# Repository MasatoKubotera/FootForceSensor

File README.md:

<html lang="en">
  <head>
    <meta charset="uft-8">
    <meta name="author" content="Masato Kubotera">
  </head>
  <body>
    <h1>FootForceSensor Ver. 1.0</h1>
    <h2>About FootForceSensor</h2>
    <p>
      FootForceSensor is a sensor that measures the pressure applied to the sole of a biped robot's foot by attaching strain gauges (load cells) to four locations on each foot.<br>
      It is under development to detect the position of the robot's center of gravity and to improve gait control.
      <h3>About Ver. 1.0</h3>
      The values of the four strain gages can be read by the Pro Micro (usable as an Aruduino Leonardo) and transferred to the computer board via a USB interface or a 3.3V system RS-485 interface to which Kondo's B3M servo motors can be connected.<br>
      Power can be supplied from the same connector as one communication, from USB bus power in the case of USB interface communication, or from Kondo's B3M servo motor connector in the case of RS-485 interface communication.<br>
      To allow left and right legs to use the same firmware, a shortland is grounded on the board to identify left and right.
      <table>
        <tr>
          <td>
            <a href="image/brd_top.png">
              <div align="center">
                
              </div>
            </a>
          </td>
          <td>
            <div align="center">
              under construction<br>
              
            </div>
          </td>
        </tr>
        <tr>
          <td>
            <div align="center">
              PCB preview image
            </div>
          </td>
          <td>
            <div align="center">
              After component mounting
            </div>
          </td>    
        </tr>
      </table>
    </p>
    <h2>Repository Contents</h2>
    <p>
    <dl>
      <dt>\image</dt>
      <dd>PCB preview images and capture of design screen</dd>
      <dt>\libraries</dt>
      <dd>Libraries used in Autodesk Eagle design</dd>
      <dt>Schematic.pdf</dt>
      <dd>Circuit diagram of this product</dd>
      <dt>BOM.txt</dt>
      <dd>Parts lists output from design data</dd>
      <dt>.brd</dt>
      <dd>Board wiring design file by Autodesk Eagle</dd>
      <dt>.sch</dt>
      <dd>Schematic design file by Autodesk Eagle</dd>
      <dt>Gerber_data.zip</dt>
      <dd>Zip folder of Gerber format files for PCB manufacturing requests.</dd>
      <dt>LICENSE</dt>
      <dd>This is a license to use this product. Please confirm before use.</dd>
      <dt>.gitignore</dt>
      <dd>File to exclude cache files from management.</dd>
    </dl>
    </p>
    <h2>Documentation</h2>
      <p>
        <h3>BOM</h3>
          <table>
            <thead>
              <tr>
                <th> Eagle Design Parts # </th>
                <th> Q'ty </th>
                <th> Mfr. Product # </th>
                <th> Supplier </th>
                <th> Description </th>
              </tr>
            </thead>
            <tbody>
              <tr>
                <td> C1, C2, C3, C5, C6, C8, C9, C10, C12, C13, C14, C16 </td>
                <td> 12 </td>
                <td> GRM188R71E105KA12 </td>
                <td> <a href="https://akizukidenshi.com/catalog/g/gP-14526/">Akizuki</a> </td>
                <td> Multilayer Ceramic Capacitors SMD/SMT 1uF 25V 10% 0603 </td>
              </tr>
              <tr>
                <td> C18, C19, C20, C21 </td>
                <td> 4 </td>
                <td> GRM188R6YA106MA73 </td>
                <td> <a href="https://akizukidenshi.com/catalog/g/gP-13161/">Akizuki</a> </td>
                <td> Multilayer Ceramic Capacitors SMD/SMT 10uF 35V 20% 0603 </td>
              </tr>
              <tr>
                <td> C4, C7, C11, C15, C17 </td>
                <td> 5 </td>
                <td> GCM188L81H104K57 </td>
                <td> <a href="https://akizukidenshi.com/catalog/g/gP-16143/">Akizuki</a> </td>
                <td> Multilayer Ceramic Capacitors SMD/SMT 0.1uF 50V 10% 0603 </td>
              </tr>
              <tr>
                <td> CH1, CH2, CH3, CH4, CH5 </td>
                <td> 5 </td>
                <td> S4B-XH-A(LF)(SN) </td>
                <td> <a href="https://akizukidenshi.com/catalog/g/gC-12842/">Akizuki</a> </td>
                <td> Connector Header Through Hole, Right Angle 4 position 2.5mm </td>
              </tr>
              <tr>
                <td> IC1, IC2, IC3, IC4 </td>
                <td> 4 </td>
                <td> HX711 </td>
                <td> <a href="https://akizukidenshi.com/catalog/g/gI-12473/">Akizuki</a> </td>
                <td> 24-Bit Analog-to-Digital Converter (ADC) for Weigh Scales </td>
              </tr>
              <tr>
                <td> IC5 </td>
                <td> 1 </td>
                <td> ADM3078E </td>
                <td> <a href="https://www.mouser.jp/ProductDetail/584-ADM3078EARZ">Mouser</a> </td>
                <td> RS-485/RS-422 Transceiver (Half Duplex, 16 Mbps, DE/RE) </td>
              </tr>
              <tr>
                <td> LED1, LED2, LED3 </td>
                <td> 3 </td>
                <td> 150060VS86000 </td>
                <td> <a href="https://www.mouser.jp/ProductDetail/710-150060VS86000">Mouser</a> </td>
                <td> Standard LEDs - SMD Green 2V 20mA 573nm 0603 </td>
              </tr>
              <tr>
                <td> M1 </td>
                <td> 1 </td>
                <td> DEV-12640 </td>
                <td> <a href="https://www.mouser.jp/ProductDetail/474-DEV-12640">Mouser</a> </td>
                <td> Development Boards & Kits - AVR Pro Micro - 5V/16MHz </td>
              </tr>
              <tr>
                <td> M1 </td>
                <td> 1 </td>
                <td> 6604S-40 </td>
                <td> <a href="https://akizukidenshi.com/catalog/g/gP-01591/">Akizuki</a> </td>
                <td> 2.54mm Pin Socket Strip, Single Row </td>
              </tr>
              <tr>
                <td> M1 </td>
                <td> 1 </td>
                <td> PHA-1x40SG </td>
                <td> <a href="https://akizukidenshi.com/catalog/g/gC-06631/">Akizuki</a> </td>
                <td> 2.54mm Pin Header Strip, Straight, Single Row </td>
              </tr>
              <tr>
                <td> R1, R4, R7, R10 </td>
                <td> 4 </td>
                <td> RC0603FR-1320KL </td>
                <td> <a href="https://www.mouser.jp/ProductDetail/603-RC0603FR-1320KL">Mouser</a> </td>
                <td> Thick Film Resistors - SMD 20 kOhms 100-200mW 1% 0603 </td>
              </tr>
              <tr>
                <td> R13, R14, R15, R16, R17, R18 </td>
                <td> 6 </td>
                <td> RC0603FR-1010KL </td>
                <td> <a href="https://www.mouser.jp/ProductDetail/603-RC0603FR-1010KL">Mouser</a> </td>
                <td> Thick Film Resistors - SMD 10 kOhms 100-200mW 1% 0603 </td>
              </tr>
              <tr>
                <td> R19, R21 </td>
                <td> 2 </td>
                <td> RC0603FR-10680RL </td>
                <td> <a href="https://www.mouser.jp/ProductDetail/603-RC0603FR-10680RL">Mouser</a> </td>
                <td> Thick Film Resistors - SMD 680 Ohms 100-200mW 1% 0603 </td>
              </tr>
              <tr>
                <td> R2, R5, R8, R11 </td>
                <td> 4 </td>
                <td> RC0603FR-138K2L </td>
                <td> <a href="https://www.mouser.jp/ProductDetail/603-RC0603FR-138K2L">Mouser</a> </td>
                <td> Thick Film Resistors - SMD 8.2 kOhms 100-200mW 1% 0603 </td>
              </tr>
              <tr>
                <td> R20 </td>
                <td> 1 </td>
                <td> RC0603FR-10120RL </td>
                <td> <a href="https://www.mouser.jp/ProductDetail/603-RC0603FR-10120RL">Mouser</a> </td>
                <td> Thick Film Resistors - SMD 120 Ohms 100-200mW 1% 0603 </td>
              </tr>
              <tr>
                <td> R3, R6, R9, R12, R22, R23, R24 </td>
                <td> 7 </td>
                <td> RC0603FR-101KL </td>
                <td> <a href="https://www.mouser.jp/ProductDetail/603-RC0603FR-101KL">Mouser</a> </td>
                <td> Thick Film Resistors - SMD 1 kOhms 100-200mW 1% 0603 </td>
              </tr>
              <tr>
                <td> T1, T2, T3, T4 </td>
                <td> 4 </td>
                <td> MMBT3906 </td>
                <td> <a href="https://akizukidenshi.com/catalog/g/gI-05967/">Akizuki</a> </td>
                <td> Bipolar Transistors - BJT Bipolar Transistor, SOT-23, 40V, 200mA, PNP </td>
              </tr>
              <tr>
                <td> T5, T6, T7 </td>
                <td> 3 </td>
                <td> BSS138 </td>
                <td> <a href="https://akizukidenshi.com/catalog/g/gI-04232/">Akizuki</a> </td>
                <td> 50V N-Channel Enhancement Mode MOSFET - ESD Protected </td>
              </tr>
              <tr>
                <td> U1 </td>
                <td> 1 </td>
                <td> LM1117GS-3.3 </td>
                <td> <a href="https://akizukidenshi.com/catalog/g/gI-16989/">Akizuki</a> </td>
                <td> LDO Voltage Regulator 3.3V 1A </td>
              </tr>
              <tr>
                <td> U2 </td>
                <td> 1 </td>
                <td> LD1117S50 </td>
                <td> <a href="https://akizukidenshi.com/catalog/g/gI-15255/">Akizuki</a> </td>
                <td> LDO Voltage Regulator 5.0V 0.8A </td>
              </tr>
            </tbody>
          </table>          
        <h3>PCB Fabrication</h3>
          PCB(Printed Circuit Board) manufacturing was outsourced to <a href="https://www.elecrow.com/pcb-manufacturing.html">Elecrow</a>.<br>
          The custom specifications are as follows.
          <ul>
            <li>Layer : 2 layers</li>
            <li>Dimensions : 50 x 40</li>
            <li>Different PCB Design : 1eg</li>
            <li>PCB Thickness : 1.6</li>
            <li>PCB Color : Black</li>
            <li>Surface Finish : HASL</li>
            <li>Castellated Hole : No</li>
            <li>Copper Weight : 1oz</li>
            <li>PCB Stencil : Stencil 10cm X 10cm no frame[Top]</li>
          </ul>
          The data used to order fabrication are as follows.
          <ul>
            <li>Eagle design rule : <a href="https://www.elecrow.com/download/Elecrow_PCB_eagle_rule.zip">Elecrow Eagle Design Rule</a></li>
            <li>Eagle CAM file : <a href="https://www.elecrow.com/download/Elecrow_Gerber_Generater_DrillAlign.zip">Elecrow CAM file</a></li>
            <li>Gerber format data : <a href="/Gerber_data.zip">Gerber_data.zip</a></li>
          </ul>
      </p>
    <h2>Contact</h2>
    <p>
    If you have any questions, please contact MasatoKubotera, the product's designer, by E-mail.<br>
    E-mail : <a href="mailto:masatokubotera06@yahoo.co.jp">masatokubotera06@yahoo.co.jp</a>
    </p>
    <h2>License Information</h2>
    <p>
      This product is open source.<br>
      Please review the <a href="/LICENSE">LICENSE file</a> for license information.<br>
      <br>
      <strong>FootForceSensor Ver. 1.0</strong> by Masato Kubotera is licensed under a <a href="http://creativecommons.org/licenses/by-nc-sa/4.0/">Creative Commons Attribution-NonCommercial-ShareAlike 4.0 International License</a>.
    </p>    
  </body>
</html>

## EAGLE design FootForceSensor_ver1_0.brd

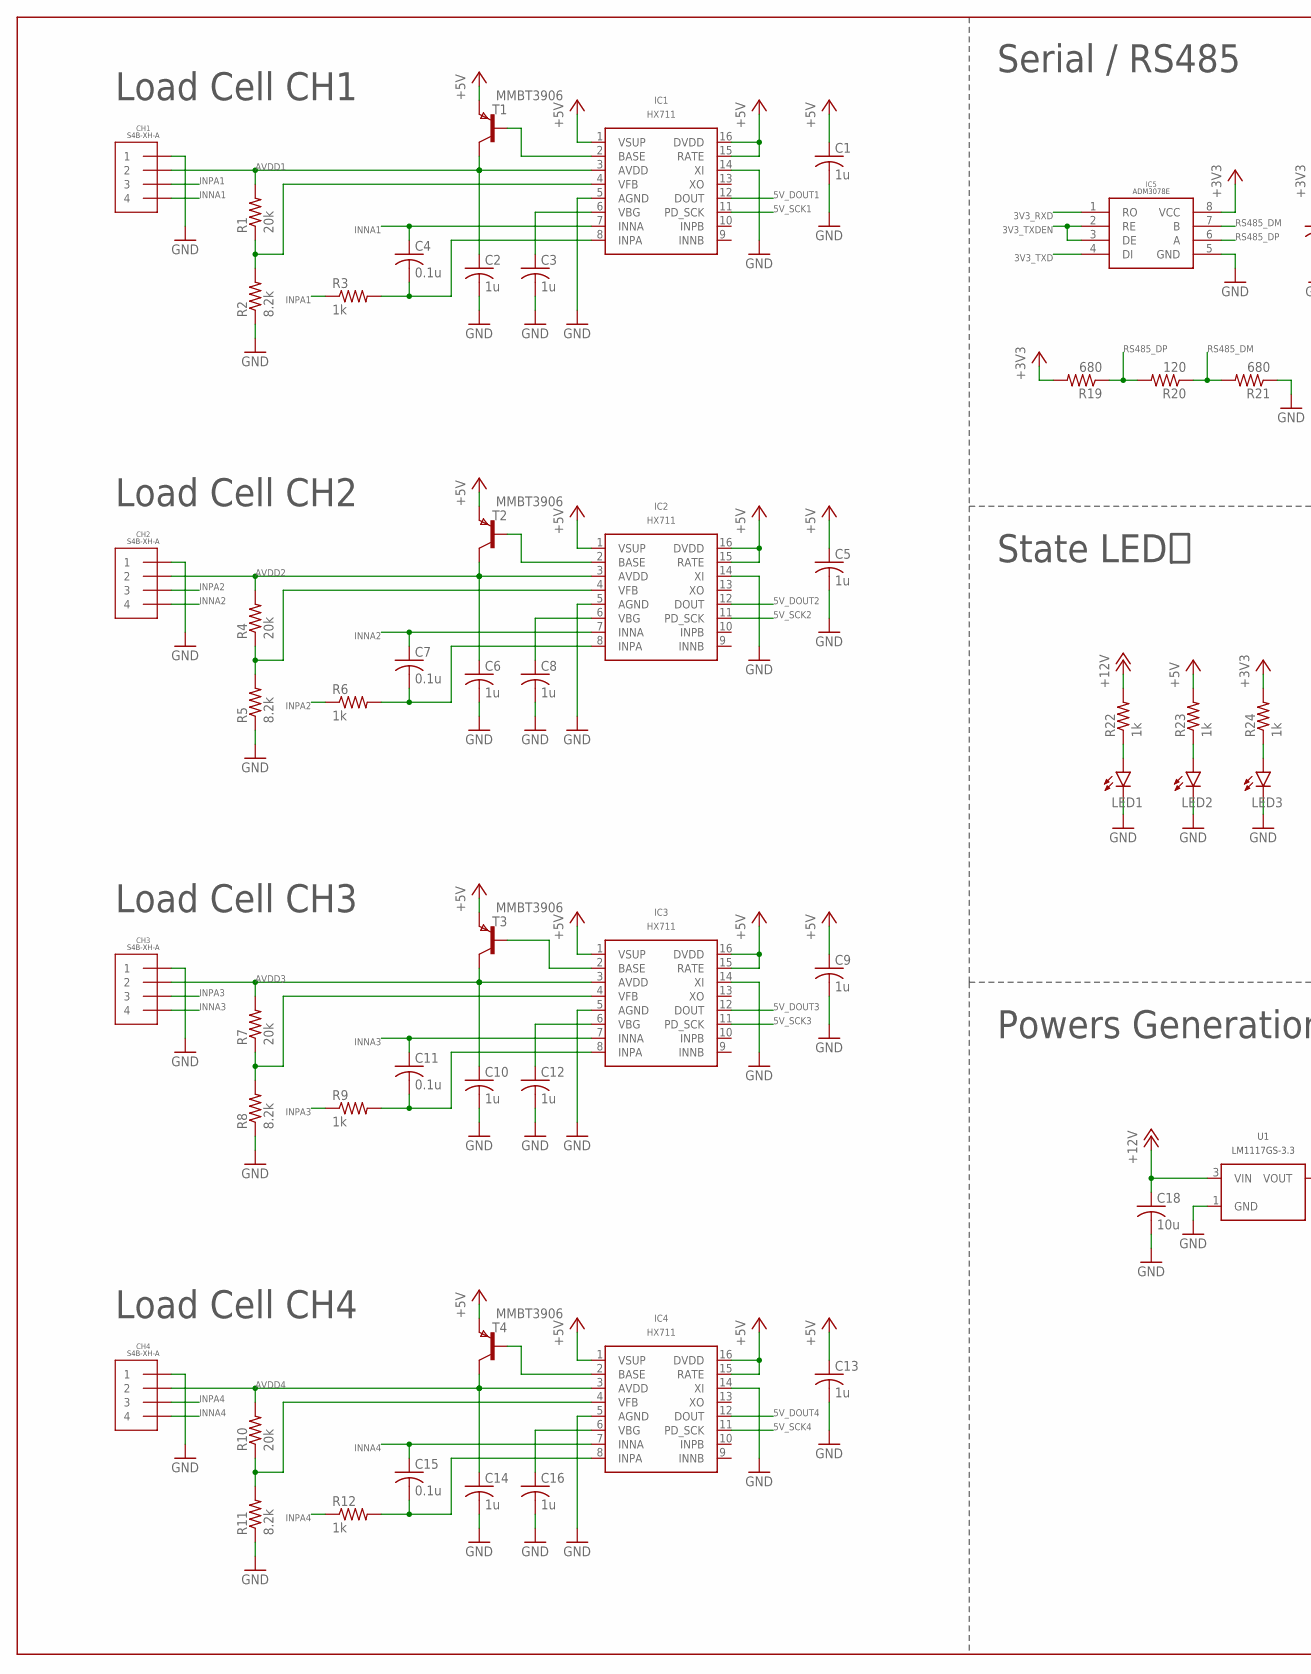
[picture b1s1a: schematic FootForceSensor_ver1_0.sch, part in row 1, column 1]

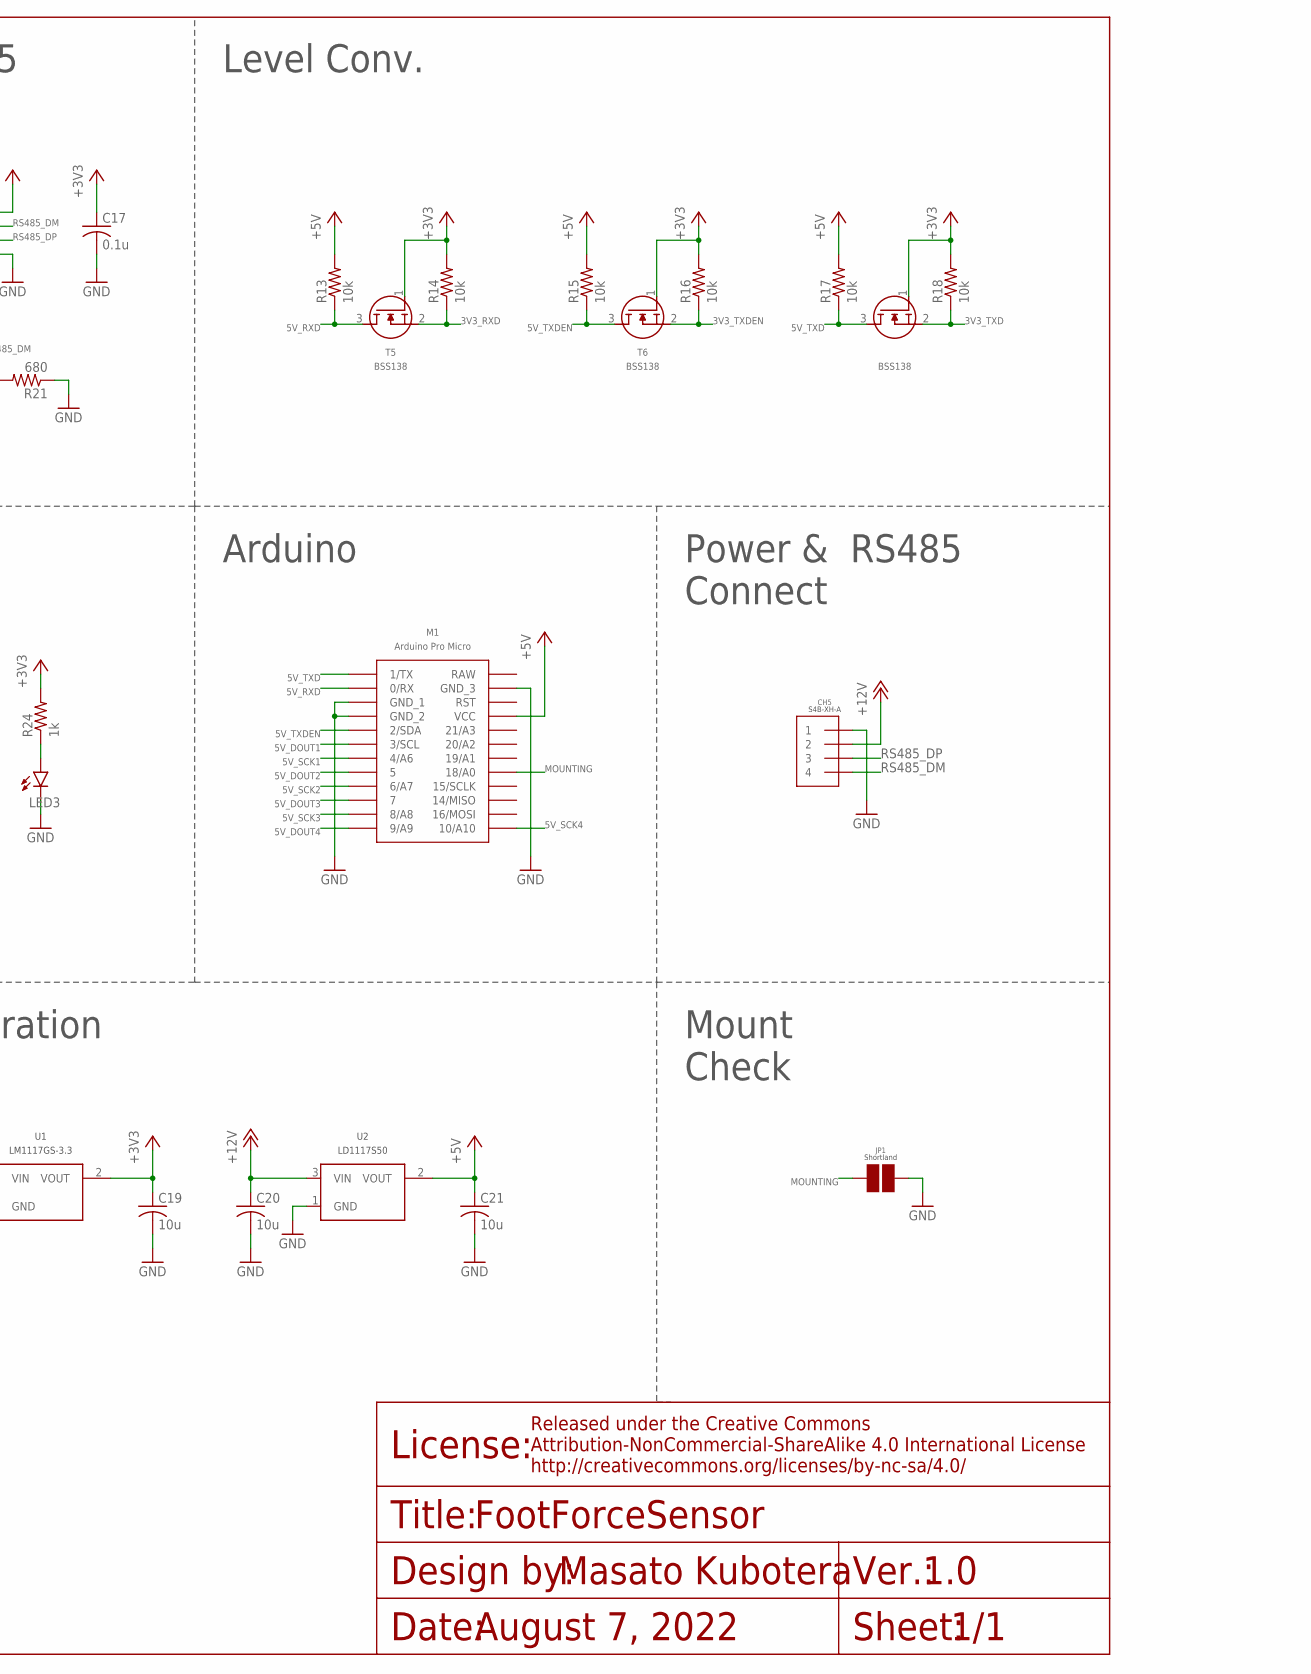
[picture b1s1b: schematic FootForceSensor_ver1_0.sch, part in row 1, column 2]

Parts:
C1, C2, C3, C5, C6, C8, C9, C10, C12, C13, C14, C16: 1u; C0603
C4, C7, C11, C15, C17: 0.1u; C0603
C18, C19, C20, C21: 10u; C0603
CH1, CH2, CH3, CH4, CH5: S4B-XH-A
IC1, IC2, IC3, IC4: HX711
IC5: ADM3078E
JP1: SHORTLAND
LED1, LED2, LED3: LEDSML0603; SML0603
M1: PRO_MICRO_THROUGH_HOLE
R1, R4, R7, R10: 20k; R0603
R2, R5, R8, R11: 8.2k; R0603
R3, R6, R9, R12, R22, R23, R24: 1k; R0603
R13, R14, R15, R16, R17, R18: 10k; R0603
R19, R21: 680; R0603
R20: 120; R0603
T1, T2, T3, T4: MMBT3906; SOT-23
T5, T6, T7: BSS138
U1: LM1117GS-3.3; SOT-223
U2: LD1117S50; SOT-223

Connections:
3V3_LED: LED3.A, R24.1
3V3_RXD: IC5.1 (RO), R14.1, T5.2 (S)
3V3_TXD: IC5.4 (DI), R18.1, T7.2 (S)
3V3_TXDEN: IC5.2 (RE), IC5.3 (DE), R16.1, T6.2 (S)
5V_DOUT1: IC1.12 (DOUT), M1.3/SCL
5V_DOUT2: IC2.12 (DOUT), M1.5
5V_DOUT3: IC3.12 (DOUT), M1.7
5V_DOUT4: IC4.12 (DOUT), M1.9/A9
5V_LED: LED2.A, R23.1
5V_RXD: M1.0/RX, R13.1, T5.3 (D)
5V_SCK1: IC1.11 (PD_SCK), M1.4/A6
5V_SCK2: IC2.11 (PD_SCK), M1.6/A7
5V_SCK3: IC3.11 (PD_SCK), M1.8/A8
5V_SCK4: IC4.11 (PD_SCK), M1.10/A10
5V_TXD: M1.1/TX, R17.1, T7.3 (D)
5V_TXDEN: M1.2/SDA, R15.1, T6.3 (D)
12V_LED: LED1.A, R22.1
+3V3: C17.1, C19.1, IC5.8 (VCC), R14.2, R16.2, R18.2, R19.2, R24.2, T5.1 (G), T6.1 (G), T7.1 (G), U1.2 (VOUT)
+5V: C1.1, C5.1, C9.1, C13.1, C21.1, IC1.1 (VSUP), IC1.15 (RATE), IC1.16 (DVDD), IC2.1 (VSUP), IC2.15 (RATE), IC2.16 (DVDD), IC3.1 (VSUP), IC3.15 (RATE), IC3.16 (DVDD), IC4.1 (VSUP), IC4.15 (RATE), IC4.16 (DVDD), M1.VCC, R13.2, R15.2, R17.2, R23.2, T1.2 (E), T2.2 (E), T3.2 (E), T4.2 (E), U2.2 (VOUT)
+12V: C18.1, C20.1, CH5.2, R22.2, U1.3 (VIN), U2.3 (VIN)
AVDD1: C2.1, CH1.2, IC1.3 (AVDD), R1.2, T1.1 (C)
AVDD2: C6.1, CH2.2, IC2.3 (AVDD), R4.2, T2.1 (C)
AVDD3: C10.1, CH3.2, IC3.3 (AVDD), R7.2, T3.1 (C)
AVDD4: C14.1, CH4.2, IC4.3 (AVDD), R10.2, T4.1 (C)
BASE1: IC1.2 (BASE), T1.3 (B)
BASE2: IC2.2 (BASE), T2.3 (B)
BASE3: IC3.2 (BASE), T3.3 (B)
BASE4: IC4.2 (BASE), T4.3 (B)
GND: C1.2, C2.2, C3.2, C5.2, C6.2, C8.2, C9.2, C10.2, C12.2, C13.2, C14.2, C16.2, C17.2, C18.2, C19.2, C20.2, C21.2, CH1.1, CH2.1, CH3.1, CH4.1, CH5.1, IC1.5 (AGND), IC1.14 (XI), IC2.5 (AGND), IC2.14 (XI), IC3.5 (AGND), IC3.14 (XI), IC4.5 (AGND), IC4.14 (XI), IC5.5 (GND), JP1.2, LED1.C, LED2.C, LED3.C, M1.GND_1, M1.GND_2, M1.GND_3, R2.1, R5.1, R8.1, R11.1, R21.1, U1.1 (GND), U2.1 (GND)
INNA1: C4.1, CH1.4, IC1.7 (INNA)
INNA2: C7.1, CH2.4, IC2.7 (INNA)
INNA3: C11.1, CH3.4, IC3.7 (INNA)
INNA4: C15.1, CH4.4, IC4.7 (INNA)
INPA1: CH1.3, R3.1
INPA1_: C4.2, IC1.8 (INPA), R3.2
INPA2: CH2.3, R6.1
INPA2_: C7.2, IC2.8 (INPA), R6.2
INPA3: CH3.3, R9.1
INPA3_: C11.2, IC3.8 (INPA), R9.2
INPA4: CH4.3, R12.1
INPA_: C15.2, IC4.8 (INPA), R12.2
MOUNTING: JP1.1, M1.18/A0
RS485_DM: CH5.4, IC5.7 (B), R20.1, R21.2
RS485_DP: CH5.3, IC5.6 (A), R19.1, R20.2
VBG1: C3.1, IC1.6 (VBG)
VBG2: C8.1, IC2.6 (VBG)
VBG3: C12.1, IC3.6 (VBG)
VBG4: C16.1, IC4.6 (VBG)
VFB1: IC1.4 (VFB), R1.1, R2.2
VFB2: IC2.4 (VFB), R4.1, R5.2
VFB3: IC3.4 (VFB), R7.1, R8.2
VFB4: IC4.4 (VFB), R10.1, R11.2

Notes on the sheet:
Load Cell CH1
Load Cell CH2
Load Cell CH3
Load Cell CH4
Serial / RS485
Powers Generation
Arduino
Level Conv.
State LEDｓ
Power & RS485 Connect
Mount Check
1.0
1/1
August 7, 2022
FootForceSensor

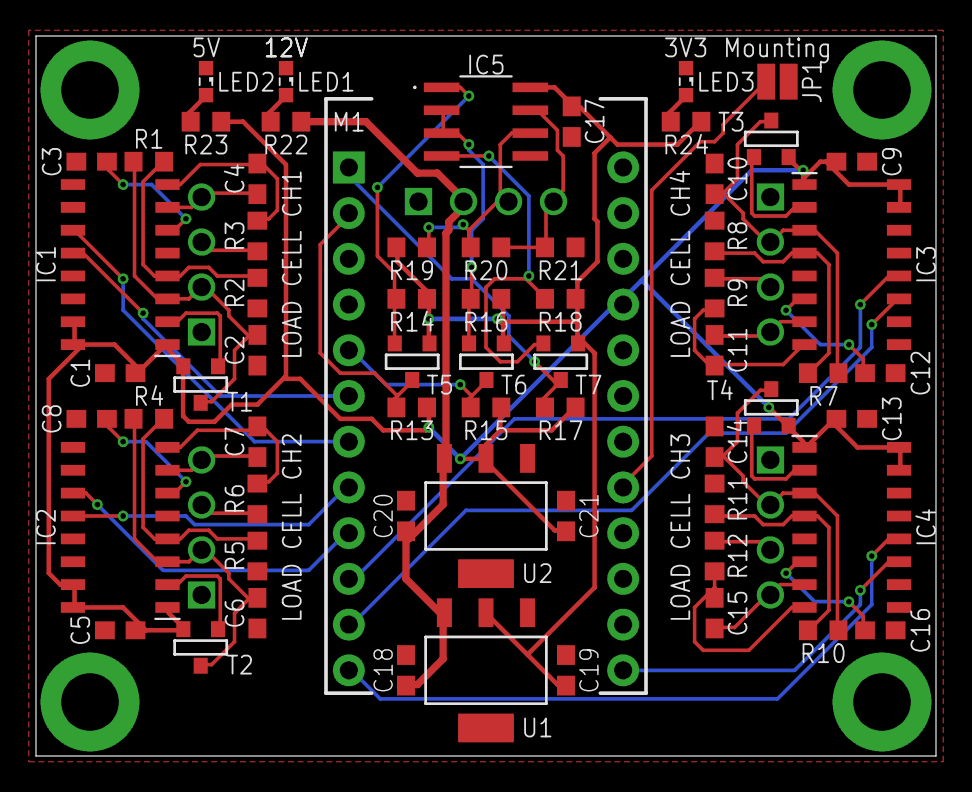
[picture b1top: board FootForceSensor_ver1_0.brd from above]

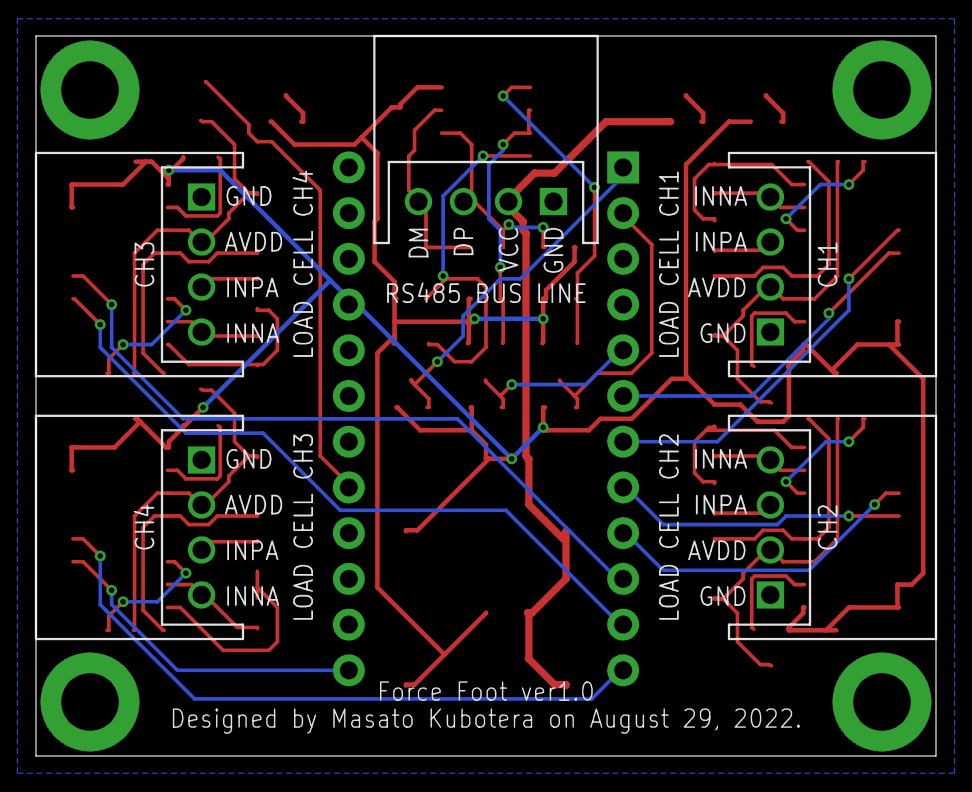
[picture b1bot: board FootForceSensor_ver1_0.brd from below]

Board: 2 copper layers, 50.0 x 40.0 mm, 69 parts (5 on the bottom side), 52 nets.

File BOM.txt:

Partlist exported from C:/Users/Masato/Documents/citbrains/FootForceSensor/FootForceSensor_ver1_0.sch at 2022/09/08 15:05

Qty Value                  Device                 Package                Parts                                               Description                
3                          LEDSML0603             SML0603                LED1, LED2, LED3                                    LED                        
5   0.1u                   C-USC0603              C0603                  C4, C7, C11, C15, C17                               CAPACITOR, American symbol 
6   10k                    R-US_R0603             R0603                  R13, R14, R15, R16, R17, R18                        RESISTOR, American symbol  
4   10u                    C-USC0603              C0603                  C18, C19, C20, C21                                  CAPACITOR, American symbol 
1   120                    R-US_R0603             R0603                  R20                                                 RESISTOR, American symbol  
7   1k                     R-US_R0603             R0603                  R3, R6, R9, R12, R22, R23, R24                      RESISTOR, American symbol  
12  1u                     C-USC0603              C0603                  C1, C2, C3, C5, C6, C8, C9, C10, C12, C13, C14, C16 CAPACITOR, American symbol 
4   20k                    R-US_R0603             R0603                  R1, R4, R7, R10                                     RESISTOR, American symbol  
2   680                    R-US_R0603             R0603                  R19, R21                                            RESISTOR, American symbol  
4   8.2k                   R-US_R0603             R0603                  R2, R5, R8, R11                                     RESISTOR, American symbol  
1   ADM3078E               ADM3078E               ADM3078E               IC5                                                                            
3   BSS138                 BSS138                 BSS138                 T5, T6, T7                                                                     
4   HX711                  HX711                  HX711                  IC1, IC2, IC3, IC4                                                             
1   LD1117S50              LD1117S50              SOT-223                U2                                                                             
1   LM1117GS-3.3           LM1117GS-3.3           SOT-223                U1                                                                             
4   MMBT3906               PNPSOT23               SOT-23                 T1, T2, T3, T4                                      PNP TRANSISTOR             
1   PRO_MICRO_THROUGH_HOLE PRO_MICRO_THROUGH_HOLE PRO_MICRO_THROUGH_HOLE M1                                                                             
5   S4B-XH-A               S4B-XH-A               S4B-XH-A               CH1, CH2, CH3, CH4, CH5                                                        
1   SHORTLAND              SHORTLAND              SHORTLAND              JP1

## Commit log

2022-08-28 Create a prototype board
2022-08-28 Create LICENSE
2022-08-29 Create Ordering Version
2022-09-13 Update LICENSE
2022-09-13 add BOM
2022-09-20 Organizing Files
2022-09-30 Maintenance of README and other public information
2022-11-21 Update URLs

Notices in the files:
parts and their libraries:
Frame: Released under the Creative Commons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
